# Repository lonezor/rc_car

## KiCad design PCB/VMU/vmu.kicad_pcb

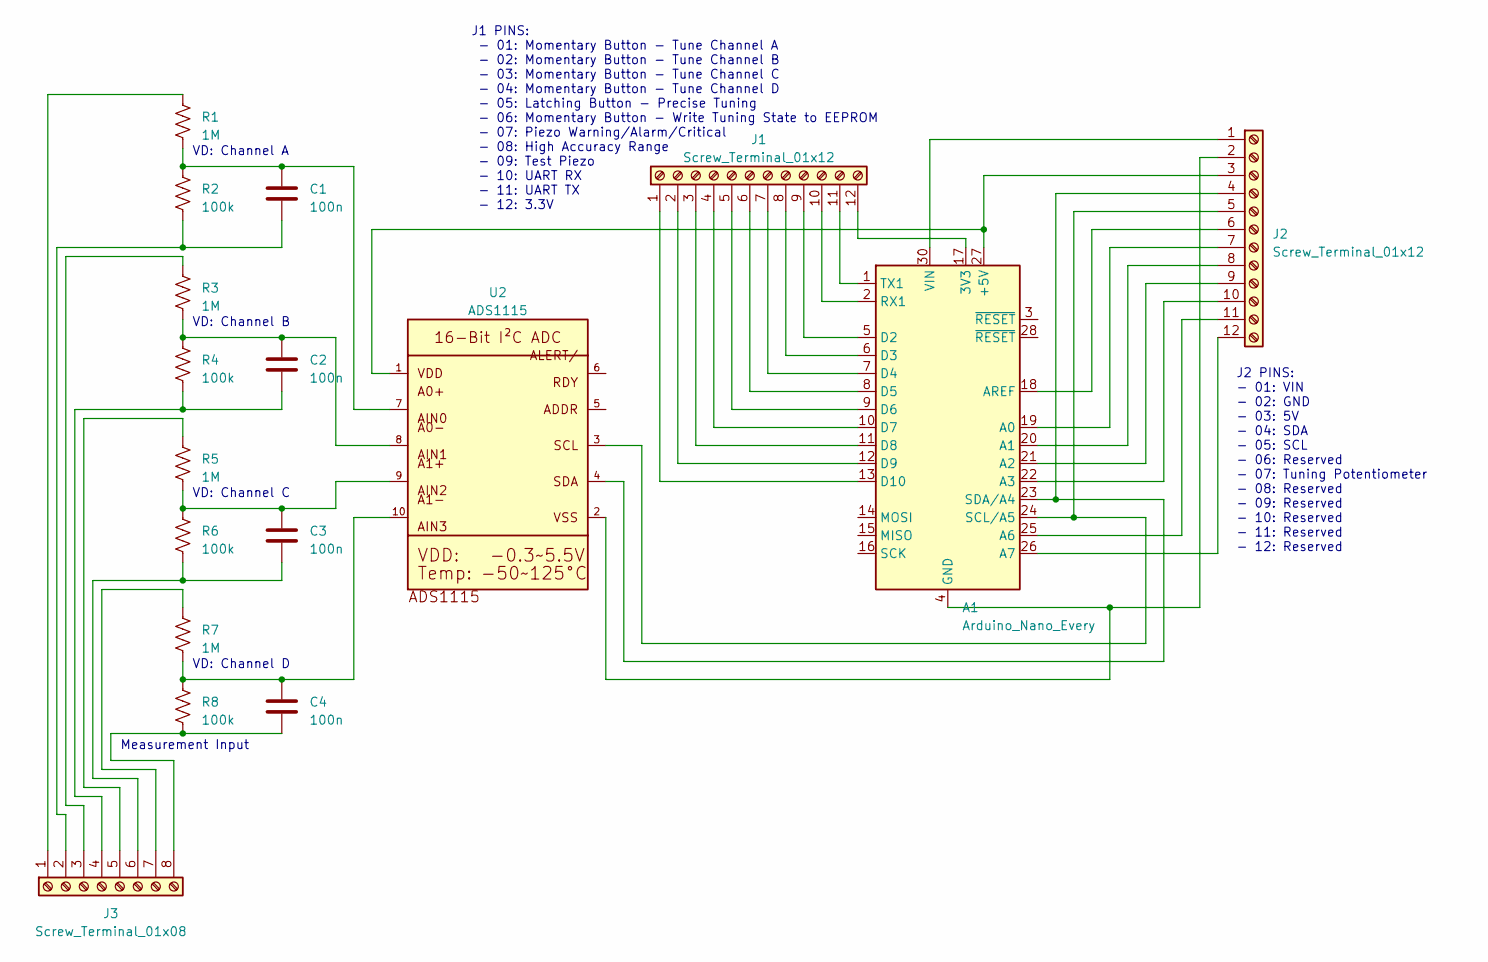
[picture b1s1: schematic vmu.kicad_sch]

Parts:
A1: Arduino_Nano_Every; Arduino_Nano_WithMountingHoles
C1, C2, C3, C4: 100n; CP_Radial_D5.0mm_P2.50mm
J1, J2: Screw_Terminal_01x12; TerminalBlock_Phoenix_MKDS-1,5-12_1x12_P5.00mm_Horizontal
J3: Screw_Terminal_01x08; TerminalBlock_Phoenix_MKDS-1,5-8_1x08_P5.00mm_Horizontal
R1, R3, R5, R7: 1M; R_Axial_DIN0207_L6.3mm_D2.5mm_P7.62mm_Horizontal
R2, R4, R6, R8: 100k; R_Axial_DIN0207_L6.3mm_D2.5mm_P7.62mm_Horizontal
U2: ADS1115; Adafruit_ADS1115

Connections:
unnamed: A1.17 (3V3), J1.12
unnamed: A1.19 (A0), J2.7
unnamed: A1.20 (A1), J2.8
unnamed: A1.21 (A2), J2.9
unnamed: A1.22 (A3), J2.10
unnamed: A1.25 (A6), J2.11
unnamed: A1.26 (A7), J2.12
unnamed: A1.18 (AREF), J2.6
unnamed: A1.5 (D2), J1.9
unnamed: A1.6 (D3), J1.8
unnamed: A1.7 (D4), J1.7
unnamed: A1.8 (D5), J1.6
unnamed: A1.9 (D6), J1.5
unnamed: A1.10 (D7), J1.4
unnamed: A1.11 (D8), J1.3
unnamed: A1.12 (D9), J1.2
unnamed: A1.13 (D10), J1.1
unnamed: A1.2 (RX1), J1.10
unnamed: A1.24 (SCL/A5), J2.5, U2.3
unnamed: A1.23 (SDA/A4), J2.4, U2.4
unnamed: A1.1 (TX1), J1.11
unnamed: A1.30 (VIN), J2.1
unnamed: C1.1, R1.2, R2.1, U2.7
unnamed: C2.1, R3.2, R4.1, U2.8
unnamed: C3.1, R5.2, R6.1, U2.9
unnamed: C4.1, R7.2, R8.1, U2.10
unnamed: A1.4 (GND), A1.29 (GND), J2.2, U2.2
unnamed: J3.1, R1.1
unnamed: C1.2, J3.2, R2.2
unnamed: J3.3, R3.1
unnamed: C2.2, J3.4, R4.2
unnamed: J3.5, R5.1
unnamed: C3.2, J3.6, R6.2
unnamed: J3.7, R7.1
unnamed: C4.2, J3.8, R8.2

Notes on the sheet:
Measurement Input
VD: Channel D
VD: Channel B
VD: Channel C
VD: Channel A
J1 PINS: - 01: Momentary Button - Tune Channel A - 02: Momentary Button - Tune Channel B - 03: Momentary Button - Tune Channel C - 04: Momentary Button - Tune Channel D - 05: Latching Button - Precise Tuning - 06: Momentary Button - Write Tuning State to EEPROM - 07: Piezo Warning/Alarm/Critical - 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
J2 PINS: - 01: VIN - 02: GND - 03: 5V - 04: SDA - 05: SCL - 06: Reserved - 07: Tuning Potentiometer - 08: Reserved - 09: Reserved - 10: Reserved - 11: Reserved - 12: Reserved

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
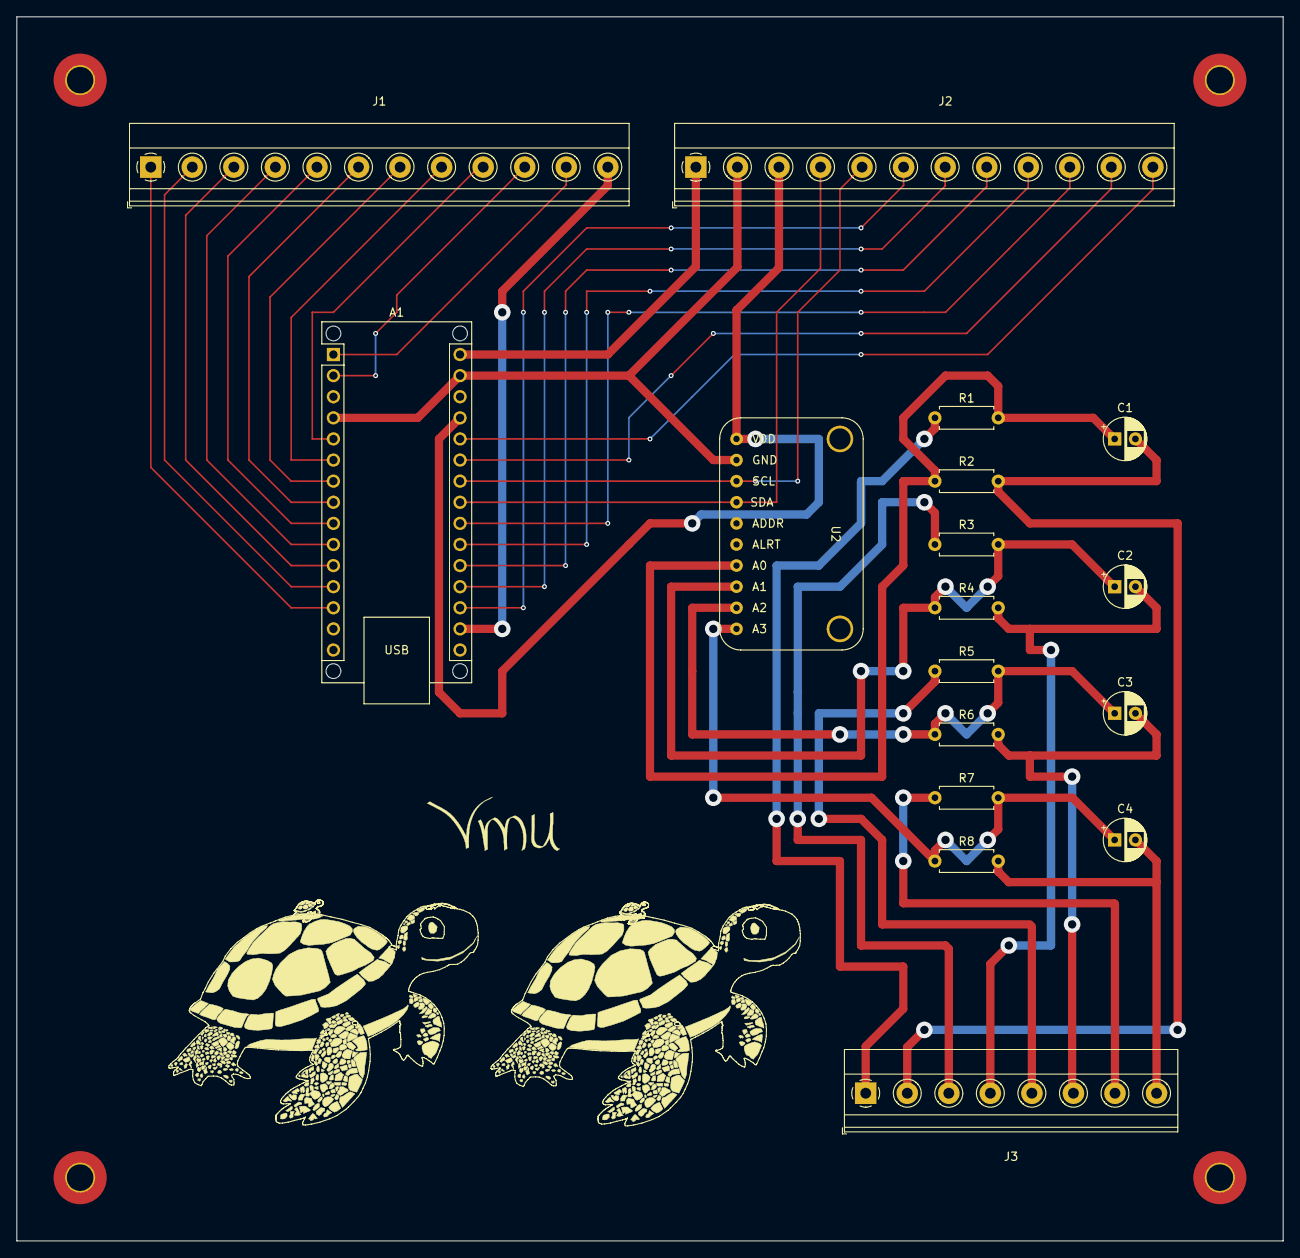
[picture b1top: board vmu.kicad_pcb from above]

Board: 2 copper layers, 152.4 x 147.3 mm, 17 parts (0 on the bottom side), 36 nets.

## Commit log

2023-03-10 Initial files and structure
2023-05-01 Working controller and introducing three vehicle build targets
2023-05-06 Add support for piezo
2023-05-06 Cleanup
2023-05-06 VMU loop changes
2023-05-06 Add PCB files for VMU
2023-07-18 Add vmu library to support future builds
